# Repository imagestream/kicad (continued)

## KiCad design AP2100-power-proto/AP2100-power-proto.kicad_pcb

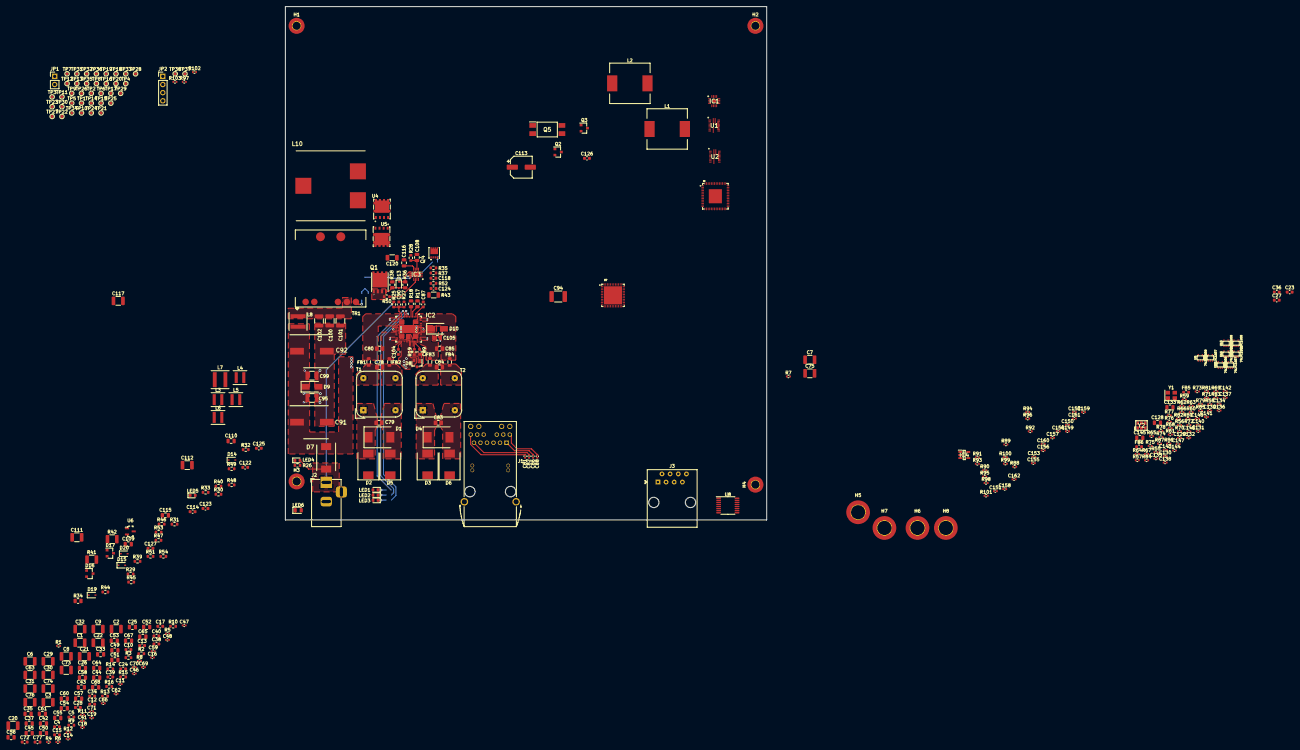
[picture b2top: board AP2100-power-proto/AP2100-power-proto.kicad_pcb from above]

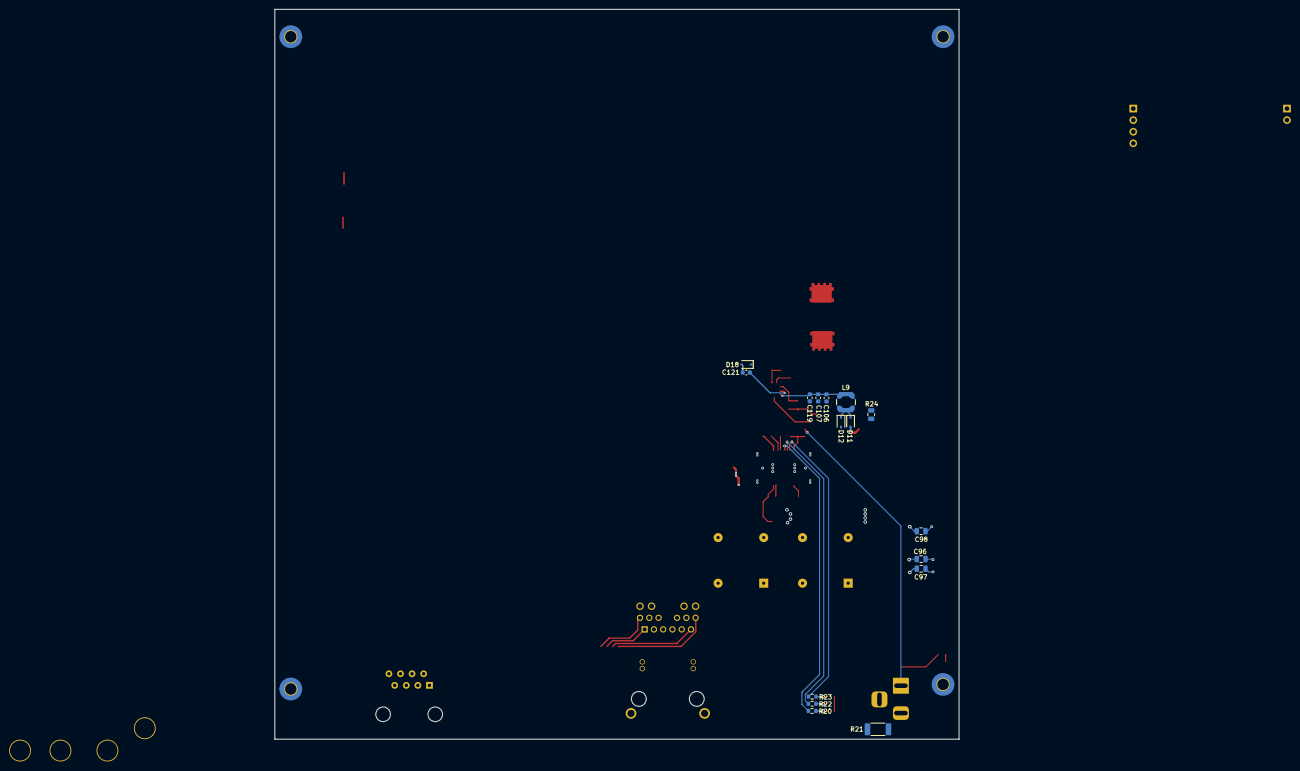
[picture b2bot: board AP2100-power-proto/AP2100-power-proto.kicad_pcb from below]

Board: 6 copper layers, 150.0 x 160.0 mm, 386 parts (16 on the bottom side), 208 nets.

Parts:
C1, C2, C3, C6, C7, C20, C21, C22, C29, C30, C73, C74: 22uF; C_1210_3225Metric
C4, C5, C12, C13, C15, C24, C28, C38, C39, C40, C72: .1uF; C_0603_1608Metric
C8, C9, C31, C32, C75: 100uF; C_1210_3225Metric
C10, C34: 500pF; C_0603_1608Metric
C11, C14, C16, C19, C69, C70, C135, C137, C139, C141: 1uF; C_0402_1005Metric
C17: .47uF; C_0603_1608Metric
C18: .22uF; C_0402_1005Metric
C23, C27, C36: 47uF; C_0603_1608Metric
C25, C26, C33, C42, C43, C44, C45, C60, C61: 4.7uF; C_0805_2012Metric
C35, C37: DNS 4.7uF; C_0805_2012Metric
C41, C46, C47, C48, C59, C62, C66, C71, C81, C82, C86, C88, C129, C130, C131, C132, C134, C136, C138, C140, C142, C149, C150, C151, C152, C153, C154, C155, C156, C157, C158, C159, C160, C161, C162: .1uF; C_0402_1005Metric
C49, C50, C51, C52, C53, C54, C55, C56, C57, C58, C64, C65, C67, C68: 22uF; C_0805_2012Metric
C63, C76: 2.2uF; C_1210_3225Metric
C77: 5600pF; C_0603_1608Metric
C78, C80, C84, C85: 33nF; C_0805_2012Metric
C79, C83, C97, C98, C108, C110, C116: 1nF; C_0805_2012Metric
C87, C89, C118: 10nF; C_0603_1608Metric
C90: 1nF; C_0603_1608Metric
C91, C92: 33uF; CAPAE1030X1050N
C94: 2200pF; C_1812_4532Metric
C95, C99, C100, C101, C102: 4.7uF; C_1210_3225Metric
C96: 100nF; C_0805_2012Metric
C104: 1.5nF; C_0603_1608Metric
C105: 10nF; C_0805_2012Metric
C106, C127: 2.2uF 25V; C_0603_1608Metric
C107, C114, C119, C121, C122, C126: 100nF; C_0603_1608Metric
C109, C115: 100pF; C_0805_2012Metric
C111, C112, C117: 47uF; C_1210_3225Metric
C113: 100uF; CP_Elec_6.3x5.9
C120: 47nF; C_1206_3216Metric
C123: 220pF; C_0603_1608Metric
C124: 100pF; C_0603_1608Metric
C125: 22nF; C_0603_1608Metric
C128, C133: 10uF; C_0805_2012Metric
C143, C144: 6.8pF; C_0402_1005Metric
C145: DNS 10uF; C_0805_2012Metric
C146, C147, C148: DNS .1uF; C_0402_1005Metric
D1, D2, D3, D4, D5, D6: SM15T68CA; D_SMC
D7: STPS4S200S; DIOM8059X265N
D8: BAV70; SOT-23
D9, D10: SMAJ58A; D_SMA
D11, D12, D13, D14, D15: BAS16J; D_SOD-323
D16, D17: BZX84C10; SOT-23
D18, D19, D20: BAS70; D_SOD-323
FB1, FB2, FB3, FB4: 220 OHM; L_0805_2012Metric
FB5: 600 OHM 500mA; L_0603_1608Metric
FB6: DNS 120 OHM 3A; L_0603_1608Metric
H1, H2, H3, H4: Mounting Hole; MountingHole_2.5mm_Pad_TopBottom
H5, H6, H7, H8: FlatAntenna; MountingHole_4.4mm_Pad_TopOnly
IC1: MAX17632BATE+; QFN50P300X300X80-17N
IC2: PM8805TR
IC3: PM8804TR; QFN50P340X340X90-17N
IC4: MIC2774N-29YM5-TR; SOT95P280X145-5N
J1: 0826-1X1T-GH-F; BEL_0826-1X1T-GH-F
J2: Barrel_Jack; BarrelJack_Horizontal
J3: RJ45; RJ45_Amphenol_54602-x08_Horizontal
JP1: I2C; PinHeader_1x02_P2.54mm_Vertical
JP2: UART; PinHeader_1x04_P2.54mm_Vertical
L1, L2: .56uH; L_13.5x12.5mm_H6mm
L3, L5, L6: 1.5uH; L_Coilcraft_XxL4040
L4: 0.6uH; L_Coilcraft_XxL4040
L7: 10uH; L_Coilcraft_XAL5030
L8: 5.6uH; L_Coilcraft_XAL5030
L9: 1mH; L_Coilcraft_LPS4018
L10: 10uH; WE-HCF_201322
LED1: T2; LED_0603_1608Metric
LED2: T1; LED_0603_1608Metric
LED3: T0; LED_0603_1608Metric
LED4: AUX; LED_0603_1608Metric
LED5: +12V; LED_0603_1608Metric
LED6: PWRLED; LED_0805_2012Metric
Q1: BSC190N15NS3GATMA1; PG-TDSON-8_1
Q2, Q3: PBSS4240T; SOT-23
Q4: FDMC86259P; FDMC86160
Q5: FOD817AS; SOP254P1016X385-4N
R1: 50K; R_0402_1005Metric
R2, R13, R27, R28, R29, R39, R40, R44: 10K; R_0603_1608Metric
R3: 90K; R_0603_1608Metric
R4, R5, R7, R81, R82, R86, R97, R102, R103: 10K; R_0402_1005Metric
R6, R8, R77, R78, R89, R90, R91, R92, R99, R100, R101: 0; R_0402_1005Metric
R9, R15: 30.1K; R_0603_1608Metric
R10, R16: 6.98K; R_0603_1608Metric
R11: 499K; R_0402_1005Metric
R12: 100K; R_0402_1005Metric
R14: 3.74K; R_0603_1608Metric
R17: 36.5; R_0805_2012Metric
R18: 150; R_0805_2012Metric
R19: 26.1K; R_0603_1608Metric
R20, R22, R23: 3.9K; R_0603_1608Metric
R21: 0; R_2010_5025Metric
R24, R36: 10; R_0805_2012Metric
R25: 100K; R_0603_1608Metric
R26, R53: 4.7K; R_0603_1608Metric
R30, R32: 1K; R_0603_1608Metric
R31, R33: 22; R_0603_1608Metric
R34: 18; R_0805_2012Metric
R35: 91K; R_0603_1608Metric
R37: 330K; R_0603_1608Metric
R38: 10K; R_0805_2012Metric
R41: 0R05; R_1210_3225Metric
R42: R100; R_1210_3225Metric
R43: 0; R_1206_3216Metric
R45, R46: 0; R_0603_1608Metric
R47: 20K; R_0603_1608Metric
R48, R50: 2K; R_0603_1608Metric
R49: 47K; R_0603_1608Metric
R51: 390; R_0603_1608Metric
R52: 130K; R_0603_1608Metric
R54: 5.23K; R_0603_1608Metric
R55, R75: 82; R_0402_1005Metric
R56, R76, R85: 110; R_0402_1005Metric
R57, R58, R59, R60, R61, R63, R72, R73: 10; R_0402_1005Metric
R62, R70, R71, R74: 1; R_0402_1005Metric
R64, R65, R66, R67, R68, R69: 49.9; R_0402_1005Metric
R79, R80: 33; R_0402_1005Metric
R83: 75; R_0402_1005Metric
R84: 56; R_0402_1005Metric
R87: DNS 10K; R_0402_1005Metric
R88, R98: 91K; R_0402_1005Metric
R93, R94: DNP 0; R_0402_1005Metric
R95: 4.7K; R_0402_1005Metric
R96: 330; R_0402_1005Metric
T1, T2: RN102-2-02-1M1; Choke_Schaffner_RN102-04-14.0x14.0mm
TP1, TP2, TP3, TP4, TP5, TP6, TP7, TP8, TP9, TP10, TP11, TP12, TP13, TP14, TP15, TP16, TP17, TP18, TP19, TP20, TP21, TP22, TP23, TP24, TP25, TP26, TP27, TP28, TP29, TP30, TP31, TP32, TP33, TP34, TP35, TP36, TP37, TP38: TestPoint; TestPoint_Pad_D1.0mm
TR1: POE120PL-12L; Transformer_Coilcraft_POE120PL
U1, U2: MPQ8634AGLE-P; QFN45P300X400X100-21N
U3: MC34VR500V4ES; QFN50P800X800X90-57N
U4, U5: STL90N6F7; TRANS_STL60P4LLF6
U6: TS2431-AILT; SOT-23-3
U7: 6V49205BNLGI; QFP50P700X700X90-49N
U8: SP3232EBEY-L/TR; TSSOP-16_4.4x5mm_P0.65mm
U9, U10, U13, U15: 74LVC1G08; SC70
U11, U12, U14, U16: 74LVC1G07; SC70
Y1: 25 MHz; Crystal_SMD_3225-4Pin_3.2x2.5mm
Y2: DNS AX3DAF1-156.2500; AX3DCF11562500

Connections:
/1V5: C53.2, C54.2, C55.2, C56.2, C57.2, C58.2, L4.1, TP34.1, U3.13 (FB1)
/1V8: C67.2, C68.2, C156.1, C157.1, C158.1, C159.1, C160.1, C161.1, C162.1, L6.1, R97.2, R98.2, R102.2, R103.2, TP24.1, U3.25 (FB2), U10.5, U11.5, U12.5, U13.5, U14.5, U15.5, U16.5
/2V5_VPP: C33.2, TP33.1, U3.28 (LDO3)
/3V3: C11.2, C14.2, C23.2, C27.2, C28.2, C29.2, C30.2, C31.2, C32.2, C34.1, C36.2, C41.2, C42.2, C43.2, C44.2, C45.2, C46.2, C47.2, C48.2, C59.2, C60.2, C61.2, C62.2, C134.1, C149.1, C154.1, C155.1, FB5.2, FB6.1, IC4.5 (VDD), L2.2, R4.2, R5.1, R13.2, R81.1, R82.1, R88.2, R95.2, TP25.1, U3.7 (PVIN1_1), U3.10 (PVIN1_2), U3.12 (PVIN1_3), U3.17 (VLDOIN1), U3.20 (PVIN4), U3.23 (PVIN2_1), U3.24 (PVIN2_2), U3.27 (VLDOIN23), U3.34 (PVIN3_1), U3.37 (PVIN3_2), U3.40 (VLDOIN45), U3.50 (VIN), U3.55 (VCCI2C), U8.16 (VCC), U9.5
/3V3_PG: R90.1, TP21.1, U2.9 (PGOOD)
/5V: C73.1, C74.1, C75.2, IC1.6 (FB), IC1.9 (EXTVCC), L7.2, TP35.1
/5V_PG: IC1.8 (~RESET), R91.1, TP20.1
/12V: C1.1, C2.1, C3.1, C20.1, C21.1, C22.1, C63.1, C111.1, C112.1, C113.1, C114.1, C117.1, D19.1 (K), IC1.1 (EN/UVLO), IC1.15 (VIN_1), IC1.16 (VIN_2), L10.2, R11.2, R29.2, R46.1, R49.2, TP36.1, U1.10 (VIN_1), U1.21 (VIN_2), U2.10 (VIN_1), U2.21 (VIN_2)
/25MHZ_CPLD: R83.2, R85.2
/25MHZ_EC1_RGMII: R80.2, TP4.1
/25MHZ_EC2_RGMII: R79.2, TP5.1
/125M_CLK: R84.2, TP1.1
/CPU_VDD_PG: R89.1, TP22.1, U1.9 (PGOOD)
/CPU_VDD_SENSE: C5.2, C6.2, C7.2, C8.2, C9.2, C10.1, L1.2, R2.2, TP26.1, TP29.1
/DDR4_RST_B: R100.2, TP19.1
/DDRCLK_18: R75.2, R76.2, TP11.1
/DDR_VREF: C69.2, TP32.1, U3.31 (REFOUT)
/DDR_VTT: C64.2, C65.2, L5.1, TP30.1, U3.19 (FB4)
/DIFF_SYSCLK_N: R73.2, TP7.1
/DIFF_SYSCLK_P: R72.2, TP9.1
/GVDD: C49.2, C50.2, C51.2, C52.2, C66.1, C70.2, L3.1, TP31.1, U3.30 (REFIN), U3.38 (FB3)
/I2C1_SCL: JP1.1, R8.2, R77.1
/I2C1_SDA: JP1.2, R6.2, R78.1
/MPCIE0_CLK_N: R58.2, R67.2, TP12.1
/MPCIE0_CLK_P: R57.2, R66.2, TP13.1
/MPCIE1_CLK_N: R60.2, R69.2, TP14.1
/MPCIE1_CLK_P: R59.2, R68.2, TP15.1
/PMIC_INT_B: R4.1, TP23.1, U3.1 (~INT~)
/PMIC_POR_B: R93.1, R99.1, U3.3 (~POR~)
/PWR_X1VDD: C25.2, TP28.1, U3.18 (LDO1)
/PoE Power/IN_12: C80.1, FB1.2, IC2.12 (IN12_1), IC2.15 (IN12_2), IC2.16 (IN12_3), IC2.EP4
/PoE Power/IN_36: C80.2, FB2.2, IC2.19 (IN36_1), IC2.20 (IN36_2), IC2.23 (IN36_3), IC2.EP3
/PoE Power/IN_45: C85.1, FB3.2, IC2.33 (IN45_1), IC2.36 (IN45_2), IC2.37 (IN45_3), IC2.EP2
/PoE Power/IN_78: C85.2, FB4.2, IC2.1 (IN78_1), IC2.40 (IN78_2), IC2.41 (IN78_3), IC2.EP1
/PoE Power/PGD: C108.1, IC2.25 (PGD), IC3.6 (PGD), R28.2
/PoE Power/VB: C87.1, IC2.2 (VB), LED1.2 (A), LED2.2 (A), LED3.2 (A), R28.1
/PoE Power/VDC: C91.1, C92.1, C95.1, C96.1, C97.1, C98.1, C99.1, D7.1, D8.2 (A), D9.1 (K), IC2.27 (VOUT_1), IC2.28 (VOUT_2), L8.1
/PoE Power/VOB: C89.2, C105.1, D8.1 (A), D10.1 (A1), IC2.17 (VOB_1), IC2.18 (VOB_2), IC2.29 (VOB_3), IC2.30 (VDD), IC2.38 (VOB_4), IC2.39 (VOB_5), IC2.EP5, IC2.EP6, R19.1
/Power/EN_VDD: C26.2, R1.1, U3.26 (LDO2)
/RST_PCIE0_B: TP17.1, U14.4
/RST_PCIE1_B: TP16.1, U16.4
/RST_eMMC_B: R101.2, TP18.1
/Reset/JTAG_RST_B_18: R97.1, U10.2
/Reset/PORESET_B_18: R98.1, U10.4, U11.2, U12.2, U13.1, U15.1
/Reset/RST_PCIE0: R102.1, U13.2
/Reset/RST_PCIE1: R103.1, U15.2
/Reset/UART_CTS: TP38.1, U8.9 (R2OUT)
/Reset/UART_RTS: TP37.1, U8.10 (T2IN)
/Reset/UART_RX: JP2.3, U8.12 (R1OUT)
/Reset/UART_TX: JP2.2, U8.11 (T1IN)
/SD1_REFCLK1_N: C147.2, TP8.1
/SD1_REFCLK1_P: C148.2, TP6.1
/SD1_REFCLK2_N: R63.2, R65.2, TP3.1
/SD1_REFCLK2_P: R61.2, R64.2, TP2.1
/SYSCLK_18: R55.2, R56.2, TP10.1
Earth: C81.1, C82.1, C86.1, C88.1, D2.1 (A1), D3.1 (A1), D5.1 (A1), D6.1 (A1), J1.21 (SHIELD), J1.22 (SHIELD), R21.2
GND: C1.2, C2.2, C3.2, C5.1, C6.1, C7.1, C8.1, C9.1, C11.1, C12.2, C13.2, C14.1, C15.1, C16.1, C17.1, C18.1, C19.1, C20.2, C21.2, C22.2, C23.1, C25.1, C26.1, C27.1, C28.1, C29.1, C30.1, C31.1, C32.1, C33.1, C35.1, C36.1, C37.1, C38.2, C39.2, C40.1, C41.1, C42.1, C43.1, C44.1, C45.1, C46.1, C47.1, C48.1, C49.1, C50.1, C51.1, C52.1, C53.1, C54.1, C55.1, C56.1, C57.1, C58.1, C59.1, C60.1, C61.1, C62.1, C63.2, C64.1, C65.1, C67.1, C68.1, C69.1, C70.1, C71.1, C73.2, C74.2, C75.1, C76.2, C77.2, C94.2, C111.2, C112.2, C113.2, C114.2, C117.2, C122.1, C127.2, C128.1, C129.2, C130.2, C131.2, C132.2, C133.1, C134.2, C135.2, C136.2, C137.2, C138.2, C139.2, C140.2, C141.2, C142.2, C143.1, C144.1, C145.1, C146.2, C149.2, C152.2, C153.2, C154.2, C155.2, C156.2, C157.2, C158.2, C159.2, C160.2, C161.2, C162.2, D16.2 (A), D17.2 (A), H1.1, H2.1, H3.1, H4.1, H5.1, H6.1, H7.1, H8.1, IC1.3 (SGND), IC1.4 (MODE/SYNC), IC1.13 (PGND_1), IC1.14 (PGND_2), IC1.17 (EP), IC4.2 (GND), J3.4, J3.5, JP2.4, LED5.1 (K), LED6.1 (K), R3.1, R7.1, R9.2, R10.1, R12.1, R14.1, R15.2, R16.1, R34.2, R39.1, R40.1, R54.2, R56.1, R64.1, R65.1, R66.1, R67.1, R68.1, R69.1, R76.1, R85.1, R86.2, TP27.1, U1.2 (AGND), U1.6 (VSNS-), U1.11 (PGND_1), U1.12 (PGND_2), U1.13 (PGND_3), U1.14 (PGND_4), U1.15 (PGND_5), U1.16 (PGND_6), U1.17 (PGND_7), U1.18 (PGND_8), U2.2 (AGND), U2.6 (VSNS-), U2.11 (PGND_1), U2.12 (PGND_2), U2.13 (PGND_3), U2.14 (PGND_4), U2.15 (PGND_5), U2.16 (PGND_6), U2.17 (PGND_7), U2.18 (PGND_8), U3.5 (ICTEST1), U3.14 (SGND1), U3.15 (SGND2), U3.32 (SGND3), U3.47 (ICTEST2), U3.48 (SGND4), U3.57 (EP), U4.1 (S_1), U4.2 (S_2), U4.3 (S_3), U5.1 (S_1), U5.2 (S_2), U5.3 (S_3), U6.3 (A), U7.3 (GND_REF1), U7.8 (GND_REF2), U7.15 (GND12_24), U7.16 (GND_2P048), U7.22 (GND_125M), U7.28 (GND_PCIE1), U7.34 (GND_PCIE2), U7.39 (GND_PCIE3), U7.40 (GND_SYS), U7.45 (GND_DDR), U7.49 (EPAD), U8.15 (GND), U9.3, U10.3, U11.3, U12.3, U13.3, U14.3, U15.3, U16.3, Y1.2, Y1.4, Y2.3 (GND)
GNDA: C116.2, C118.1, C124.1, C126.1, IC3.1 (AGND), IC3.17 (EP), Q5.3, R35.1, R37.1, R43.2, R52.1
GNDPWR: C87.2, C90.2, C91.2, C92.2, C94.1, C95.2, C96.2, C97.2, C98.2, C99.2, C100.2, C101.2, C102.2, C104.1, C105.2, C106.2, C107.2, C108.2, C119.2, D9.2 (A), D10.2 (A2), D12.2 (A), D18.1 (K), IC2.3 (STBY), IC2.6 (AGND), IC2.10 (FAUX), IC2.13 (GND12_1), IC2.14 (GND12_2), IC2.21 (GND36_1), IC2.22 (GND36_2), IC2.34 (GND45_1), IC2.35 (GND45_2), IC2.42 (GND78_1), IC2.43 (GND78_2), IC3.10 (PGND), J2.2, Q4.1 (S_1), Q4.2 (S_2), Q4.3 (S_3), R17.2, R18.2, R21.1, R26.2, R27.2, R38.1, R41.1, R42.1, R43.1, R44.1, TR1.1
unnamed: C4.1, L1.1, U1.20 (SW)
unnamed: C4.2, U1.1 (BST)
unnamed: C10.2, R2.1, R3.2, U1.7 (FB)
unnamed: C12.1, U1.19 (VCC)
unnamed: C13.1, C15.2, U1.5 (TRK/REF)
unnamed: C16.2, U3.51 (VDIG)
unnamed: C17.2, U3.43 (VBIAS)
unnamed: C18.2, U3.52 (VBG)
unnamed: C19.2, U3.49 (VCC)
unnamed: C24.1, L2.1, U2.20 (SW)
unnamed: C24.2, U2.1 (BST)
unnamed: C34.2, R13.1, R14.2, U2.7 (FB)
unnamed: C35.2, U3.39 (LDO4)
unnamed: C37.2, U3.41 (LDO5)
unnamed: C38.1, U2.19 (VCC)
unnamed: C39.1, C40.2, U2.5 (TRK/REF)
unnamed: C66.2, C71.2, U3.29 (VHALF)
unnamed: C72.1, IC1.11 (LX_1), IC1.12 (LX_2), L7.1
unnamed: C72.2, IC1.10 (BST)
unnamed: C76.1, IC1.2 (VCC)
unnamed: C77.1, IC1.5 (SS)
unnamed: C78.1, FB1.1, T1.2
unnamed: C78.2, FB2.1, T1.4
unnamed: C79.1, D1.1 (A1), D2.2 (A2), J1.13 (VC1), T1.1
unnamed: C79.2, D1.2 (A2), D5.2 (A2), J1.14 (VC2), T1.3
unnamed: C81.2, J1.12 (TRCT1)
unnamed: C82.2, J1.6 (TRCT2)
unnamed: C83.1, D3.2 (A2), D4.1 (A1), J1.15 (VC3), T2.1
unnamed: C83.2, D4.2 (A2), D6.2 (A2), J1.16 (VC4), T2.3
unnamed: C84.1, FB3.1, T2.2
unnamed: C84.2, FB4.1, T2.4
unnamed: C86.2, J1.1 (TRCT3)
unnamed: C88.2, J1.7 (TRCT4)
unnamed: C89.1, D8.3 (K), IC2.32 (VCP)
unnamed: C90.1, IC2.11 (RAUX), R25.1, R27.1
unnamed: C100.1, C101.1, C102.1, L8.2, R24.2, TR1.5
unnamed: C104.2, IC2.24 (CTRL)
unnamed: C106.1, C107.1, C119.1, IC3.12 (VC), L9.1
unnamed: C109.1, D14.1 (K), R30.1, R31.1, TR1.8, U5.5 (D_1), U5.6 (D_2), U5.7 (D_3), U5.8 (D_4)
unnamed: C109.2, D16.1 (K), Q2.1 (B), R30.2
unnamed: C110.1, C115.1, D15.1 (K), L10.1, R32.1, R33.1, TR1.10, U4.5 (D_1), U4.6 (D_2), U4.7 (D_3), U4.8 (D_4)
unnamed: C110.2, R34.1
unnamed: C115.2, D17.1 (K), Q3.1 (B), R32.2
unnamed: C116.1, IC3.8 (VIN), R24.1
unnamed: C118.2, IC3.2 (SS)
unnamed: C120.1, Q4.5 (D_1), Q4.6 (D_2), Q4.7 (D_3), Q4.8 (D_4)
unnamed: C120.2, Q1.5 (D_1), Q1.6 (D_2), Q1.7 (D_3), Q1.8 (D_4), TR1.2
unnamed: C121.1, D18.2 (A), Q4.4 (G), R44.2
unnamed: C121.2, IC3.11 (GAT2)
unnamed: C122.2, Q5.1, R45.2
unnamed: C123.1, R47.1, R53.1, R54.1, U6.2 (REF)
unnamed: C123.2, C125.2, D20.2 (A), R48.1, U6.1 (K)
unnamed: C124.2, IC3.14 (CS), R50.2
unnamed: C125.1, R53.2
unnamed: C126.2, R51.2
unnamed: C127.1, D19.2 (A), D20.1 (K), R49.1
unnamed: C128.2, C129.1, C130.1, C131.1, C132.1, C133.2, FB5.1, R62.1, R70.1, R71.1, R74.1, U7.7 (VDD_REF1), U7.19 (VDD_2P048), U7.27 (VDD_PCIE), U7.43 (VDD_DDR), U7.48 (VDD_REF2)
unnamed: C135.1, C136.1, R62.2, U7.42 (AVDD_SYS)
unnamed: C137.1, C138.1, R70.2, U7.33 (AVDD_PCIE)
unnamed: C139.1, C140.1, R71.2, U7.20 (AVDD_125)
unnamed: C141.1, C142.1, R74.2, U7.12 (AVDD12_24)
unnamed: C143.2, U7.2 (X1_25), Y1.3
unnamed: C144.2, U7.1 (X2_25), Y1.1
unnamed: C145.2, C146.1, FB6.2, R87.2, Y2.6 (VDD)
unnamed: C147.1, Y2.5 (CLK#)
unnamed: C148.1, Y2.4 (CLK)
unnamed: C150.1, U8.1 (C1+)
unnamed: C150.2, U8.3 (C1-)
unnamed: C151.1, U8.4 (C2+)
unnamed: C151.2, U8.5 (C2-)
unnamed: C152.1, U8.2 (VS+)
unnamed: C153.1, U8.6 (VS-)
unnamed: D7.2, J2.1, LED4.2 (A), R25.2
unnamed: D11.1 (K), D12.1 (K), L9.2
unnamed: D11.2 (A), TR1.6
unnamed: D13.1 (K), IC3.9 (GAT1), R36.1
unnamed: D13.2 (A), Q1.4 (G), R36.2, R38.2
unnamed: D14.2 (A), Q2.2 (E), R39.2, U4.4 (G)
unnamed: D15.2 (A), Q3.2 (E), R40.2, U5.4 (G)
unnamed: IC2.4 (CLS1), R17.1
unnamed: IC2.5 (CLS2), R18.1
unnamed: IC2.7 (T0), R20.1
unnamed: IC2.8 (T1), R22.1
unnamed: IC2.9 (T2), R23.1
unnamed: IC2.31 (DET), R19.2
unnamed: IC3.3 (DT), R37.2
unnamed: IC3.4 (FSW), R35.2
unnamed: IC3.15 (CTL), Q5.4, R51.1
unnamed: IC3.16 (BLK), R52.2
unnamed: IC4.1 (~RST), R92.1
unnamed: IC4.3 (~MR), R93.2, R95.1, U9.2
unnamed: IC4.4 (IN), R88.1, R89.2, R90.2, R91.2, U9.1
unnamed: J3.1, U8.7 (T2OUT)
unnamed: J3.2, R94.2
unnamed: J3.3, U8.14 (T1OUT)
unnamed: J3.6, U8.13 (R1IN)
unnamed: J3.7, R94.1
unnamed: J3.8, U8.8 (R2IN)
unnamed: L3.2, U3.35 (LX3_1), U3.36 (LX3_2)
unnamed: L4.2, U3.8 (LX1_1), U3.9 (LX1_2), U3.11 (LX1_3)
unnamed: L5.2, U3.21 (LX4)
unnamed: L6.2, U3.22 (LX2)
unnamed: LED1.1 (K), R23.2
unnamed: LED2.1 (K), R22.2
unnamed: LED3.1 (K), R20.2
unnamed: LED4.1 (K), R26.1
unnamed: LED5.2 (A), R29.1
unnamed: LED6.2 (A), R96.1
unnamed: Q1.1 (S_1), Q1.2 (S_2), Q1.3 (S_3), R41.2, R42.2, R50.1
unnamed: Q2.3 (C), R31.2
unnamed: Q3.3 (C), R33.2
unnamed: Q5.2, R48.2
unnamed: R1.2, U1.8 (EN)
unnamed: R5.2, U3.56 (EN)
unnamed: R6.1, U3.53 (SDA)
unnamed: R7.2, U3.4 (STBY)
unnamed: R8.1, U3.54 (SCL)
unnamed: R9.1, U1.4 (MODE)
unnamed: R10.2, U1.3 (CS)
unnamed: R11.1, R12.2, U2.8 (EN)
unnamed: R15.1, U2.4 (MODE)
unnamed: R16.2, U2.3 (CS)
unnamed: R45.1, R46.2, R47.2
unnamed: R55.1, U7.41 (SYS_CCB)
unnamed: R57.1, U7.23 (PCIET_LR0)
unnamed: R58.1, U7.24 (PCIEC_LR0)
unnamed: R59.1, U7.26 (PCIET_LR1)
unnamed: R60.1, U7.25 (PCIEC_LR1)
unnamed: R61.1, U7.30 (PCIET_LR2)
unnamed: R63.1, U7.29 (PCIEC_LR2)
unnamed: R72.1, U7.32 (PCIET_LR3)
unnamed: R73.1, U7.31 (PCIEC_LR3)
unnamed: R75.1, U7.44 (SEL100#_66/DDRCLK)
unnamed: R77.2, U7.46 (SCLK)
unnamed: R78.2, U7.47 (SDATA)
unnamed: R79.1, U7.10 (REF_1)
unnamed: R80.1, U7.9 (REF_2)
unnamed: R81.2, U7.13 (FS0/USB_CLK1)
unnamed: R82.2, U7.11 (SELPCIE125#_100/REF_0)
unnamed: R83.1, U7.4 (REF_5)
unnamed: R84.1, U7.21 (125M)
unnamed: R86.1, U7.14 (FS1/USB_CLK2)
unnamed: R87.1, Y2.1 (OE1)
unnamed: R96.2, U9.4
unnamed: R99.2, U10.1
unnamed: R100.1, U11.4
unnamed: R101.1, U12.4
unnamed: U13.4, U14.2
unnamed: U15.4, U16.2

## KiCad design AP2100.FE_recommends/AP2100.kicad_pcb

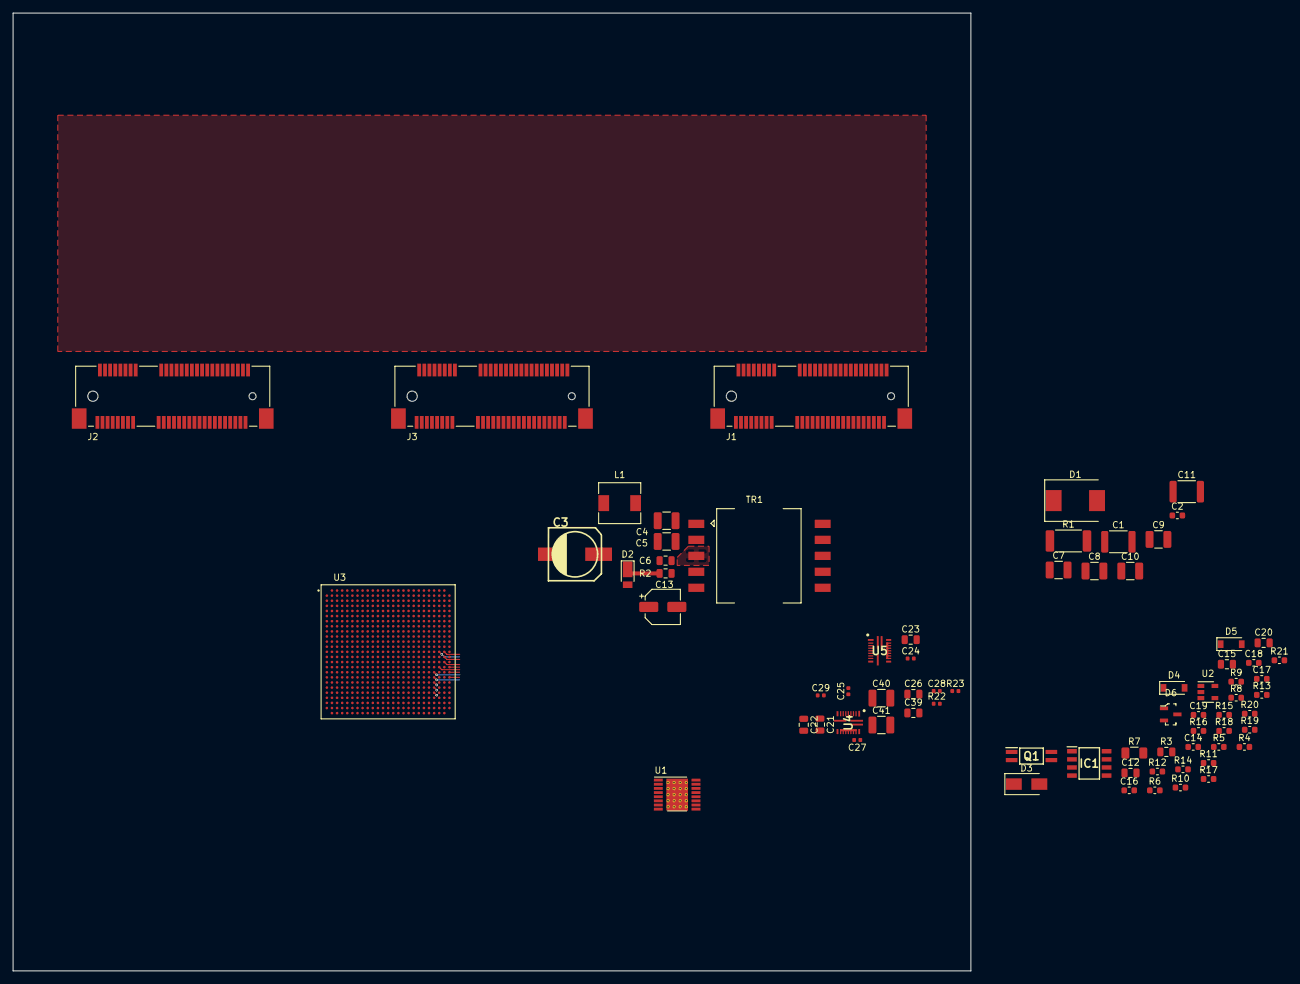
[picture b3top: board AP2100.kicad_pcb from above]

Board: 6 copper layers, 150.0 x 150.0 mm, 73 parts (0 on the bottom side), 40 nets.

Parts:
C1, C11: 2.2nF; C_1812_4532Metric
C2: 2.2nF; C_0603_1608Metric
C3: EEEFK2A220P; EEEFK2A220P_FKV(F)
C4, C5: 2.2uF; C_1210_3225Metric
C6, C12: 100nF; C_0805_2012Metric
C7, C8, C9, C10: 22uf; C_1210_3225Metric
C13: 22uF; CP_Elec_5x5.3
C14: 470nF; C_0603_1608Metric
C15, C20: 1uF; C_0805_2012Metric
C16: 100pF; C_0603_1608Metric
C17: 330pF; C_0603_1608Metric
C18: 22nF; C_0603_1608Metric
C19: 33nF; C_0603_1608Metric
C21, C22, C23, C26, C39: 22uF; C_0805_2012Metric
C24, C25, C28, C29: .1uF; C_0402_1005Metric
C27: .1; C_0402_1005Metric
C40, C41: 100uF; C_1210_3225Metric
D1: SK86; D_SMC
D2: DFLU1200-7; D_PowerDI-123
D3: SMAJ58A_C151930; D_SMA
D4, D5: MMSD4148T1G; D_SOD-123
D6: BAT54S-7-F; SOT-23-3
IC1: FDS86242; SOIC127P600X175-8N
J1, J2, J3: Bus_PCI_Express_Mini; BUS_PCI_Express_Mini_Full
L1: 3.3uH; L_6.0x6.0_H2
Q1: HMHA2801AR2; SOIC127P680X239-4N
R1: 7.5; R_2512_6332Metric
R2: 39K; R_0805_2012Metric
R3: 20; R_0805_2012Metric
R4: 750K; R_0603_1608Metric
R5: 24.9K; R_0603_1608Metric
R6: 0; R_0603_1608Metric
R7: .082; R_1206_3216Metric
R8: 63.4; R_0603_1608Metric
R9: 100K; R_0603_1608Metric
R10: 332; R_0603_1608Metric
R11: 10; R_0603_1608Metric
R12, R19, R20: 2K; R_0603_1608Metric
R13, R15: 10K; R_0603_1608Metric
R14: 4.99K; R_0603_1608Metric
R16: 4.42K; R_0603_1608Metric
R17: 34K; R_0603_1608Metric
R18: 1K; R_0603_1608Metric
R21: 2.61K; R_0603_1608Metric
R22: 30.1K; R_0402_1005Metric
R23: 6.98K; R_0402_1005Metric
TR1: TSE265; Transformer_TNK_TSE265
U1: TPS23751PWP
U2: TL431DBV; SOT-23-5
U3: LS1043ASE7KQB; BGA621C80P25X25_2100X2100X192N
U4, U5: MPQ8634AGLE-P; QFN45P300X400X100-21N

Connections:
/PoE Power/V12: C2.1, C7.1, C8.1, C9.1, C10.1, D1.1, R6.2
/PoE Power/VB: C14.2, C18.2, R20.1, U1.10
/Power/+12V: C21.1, C22.1, C23.1, U4.10, U4.21, U5.10, U5.21
/Power/CPU_VDD: C25.2, C26.2, C39.2, C40.2, C41.2, U4.7
GND: C7.2, C8.2, C9.2, C10.2, C11.2, C20.2, C21.2, C22.2, C23.2, C25.1, C26.1, C27.2, C28.2, C29.1, C39.1, C40.1, C41.1, R21.1, R22.2, R23.1, TR1.9, TR1.10, U2.5, U4.2, U4.6, U4.11, U4.12, U4.13, U4.14, U4.15, U4.16, U4.17, U4.18, U5.2, U5.11, U5.12, U5.13, U5.14, U5.15, U5.16, U5.17, U5.18
GNDPWR: C1.2, C3.2, C4.2, C5.2, C11.1, C13.2, C14.1, C15.1, C17.1, Q1.3, R7.1, R16.1, R17.1, TR1.4, U1.9, U1.14, U1.15
unnamed: C1.1, C4.1, C5.1, C6.1, L1.2, R2.1, TR1.1
unnamed: C2.2, R1.1
unnamed: C6.2, D2.2, IC1.5, IC1.6, IC1.7, IC1.8, TR1.3
unnamed: C3.1, C12.1, D3.1, L1.1, R4.1, R5.2, U1.1
unnamed: C12.2, D3.2, R8.2, U1.16, U1.17
unnamed: C13.1, C15.2, D4.1, U1.12
unnamed: C16.1, C20.1, D6.1, D6.3, Q1.2, R13.2, R14.2, R18.2, U2.3
unnamed: C16.2, C19.2, R15.1, R21.2, U2.4
unnamed: C17.2, R4.2, R10.1, U1.11
unnamed: C18.1, R19.1
unnamed: C19.1, R18.1
unnamed: C24.1, U4.20
unnamed: C24.2, U4.1
unnamed: C27.1, U4.19
unnamed: C28.1, C29.2, U4.5
unnamed: D1.2, R1.2, TR1.6, TR1.7
unnamed: D2.1, R2.2
unnamed: D4.2, R3.2
unnamed: D5.1, R11.1, U1.13
unnamed: D5.2, IC1.4, R11.2
unnamed: D6.2, R6.1, R12.1, R13.1, R14.1, R15.2
unnamed: IC1.1, IC1.2, IC1.3, R7.2, R10.2
unnamed: J1.4, J1.9, J1.15, J1.18, J1.21, J1.26, J1.27, J1.29, J1.34, J1.35, J1.37, J1.40, J1.43, J1.50
unnamed: J2.4, J2.9, J2.15, J2.18, J2.21, J2.26, J2.27, J2.29, J2.34, J2.35, J2.37, J2.40, J2.43, J2.50
unnamed: J3.4, J3.9, J3.15, J3.18, J3.21, J3.26, J3.27, J3.29, J3.34, J3.35, J3.37, J3.40, J3.43, J3.50
unnamed: Q1.1, R12.2
unnamed: Q1.4, R19.2, R20.2, U1.8
unnamed: R3.1, TR1.5
unnamed: R5.1, U1.2
unnamed: R8.1, U1.3
unnamed: R9.1, R16.2, U1.4
unnamed: R17.2, U1.5
unnamed: R22.1, U4.4
unnamed: R23.2, U4.3

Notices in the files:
parts and their libraries:
Copyright 2016 Accelerated Designs. All rights reserved.
